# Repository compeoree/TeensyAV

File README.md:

# TeensyAV
A two-layer printed circuit board that breaks out a Teensy 3.5 or 3.6. Its primary goal is to provide a front end for the [Teensy Convolution Sofware Defined Radio](https://github.com/compeoree/Teensy-ConvolutionSDR), but can be used for any audio/video project. 

# UNTESTED!
This is a work in progress and has yet to be fabricated, assembled, or tested.

# Easy Method
* Order PCB through [OSHPark](https://oshpark.com/shared_projects/IBIkLilf)

# DIY Method
* Install KiCad version 5 (http://kicad-pcb.org/download/)
* Copy Library and Modules to KiCad install directory (usually {install_location}/KiCad/share/kicad/)
* Open TeensyAV.pro project file

## BOM (Total price approximately $90)
* PCB ([$18.68](https://oshpark.com/shared_projects/IBIkLilf))
* U1 Teensy 3.6 ([$29.25](https://www.pjrc.com/store/teensy36.html))
* J1 Audio Board ([$14.25](https://www.pjrc.com/store/teensy3_audio.html))
* U2 Touchscreen ([$15.00](https://www.pjrc.com/store/display_ili9341_touch.html))
* Q1 Si2371EDS MOSFET ([$0.49](https://www.mouser.com/ProductDetail/78-SI2371EDS-T1-GE3))
* Q2 BSR802N MOSFET ([$0.46](https://www.mouser.com/ProductDetail/726-BSR802NL6327))
* S1,S2,S3,S4,S5,S7 Switches ([$0.25](https://www.mouser.com/ProductDetail/653-B3F-1000))
* SW1,SW2,SW3 Magnetic Encoder ([$1.14](https://www.mouser.com/ProductDetail/858-EN12-HS22AF20))
* SW4 Optional Optical Encoder ([$28.30](https://www.mouser.com/ProductDetail/652-EM14A0D-B28L064N))
* R1,R2,R3,R4 10K SMD Resistor ([$0.10](https://www.mouser.com/ProductDetail/603-RC0603FR-0710KL))
* CR2032 RTC Battery and Holder ([$0.29](https://www.mouser.com/ProductDetail/712-BAT-HLD-001))
* J1,J2 SMD male headers ([$2.10](https://www.mouser.com/ProductDetail/710-61001418221))
* U1 SMD male headers (left) ([$3.61](https://www.mouser.com/ProductDetail/710-61002418221))

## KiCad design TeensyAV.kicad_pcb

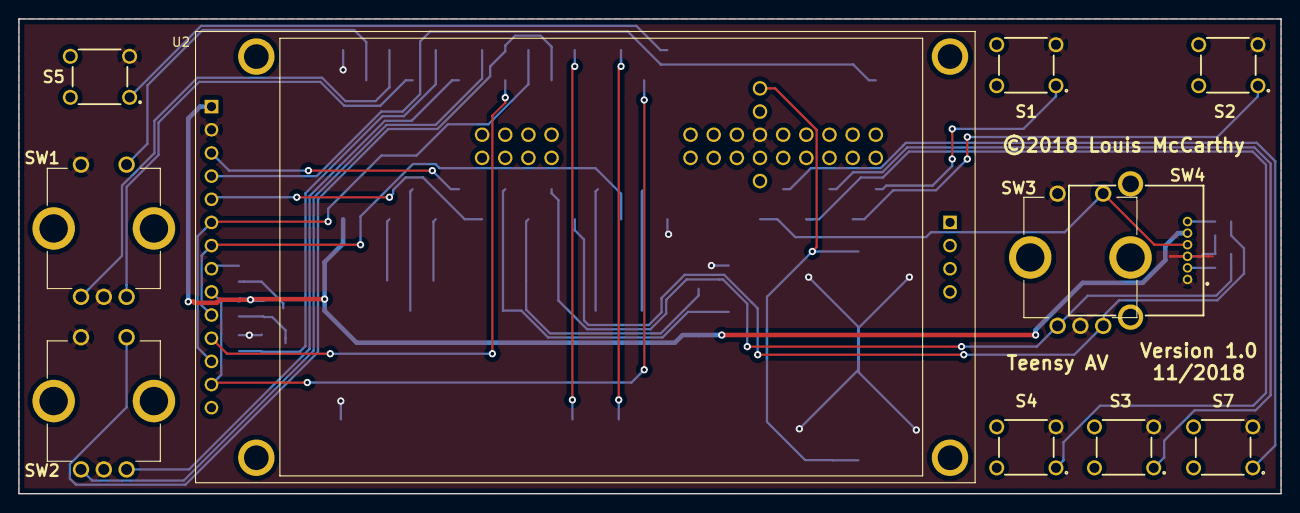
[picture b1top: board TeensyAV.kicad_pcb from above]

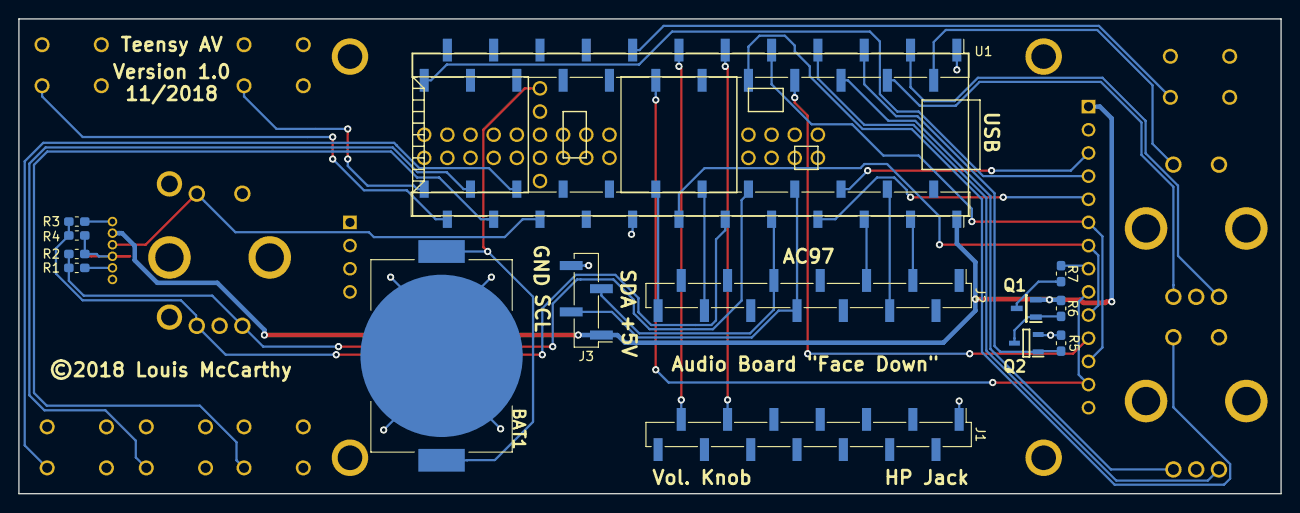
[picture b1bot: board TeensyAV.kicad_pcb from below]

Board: 2 copper layers, 138.4 x 52.1 mm, 25 parts (14 on the bottom side), 40 nets.

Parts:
BAT1: BAT-HLD-001; BATHLD001
J1, J2: Conn_01x14_Male; PinHeader_1x14_P2.54mm_Vertical_SMD_Pin1Left
J3: Conn_01x04_Male; PinHeader_1x04_P2.54mm_Vertical_SMD_Pin1Left
Q1: SI2371EDS-T1-GE3; SOT95P237X112-3N
Q2: BSR802N_L6327; SOT95P285X120-3N
R1, R2, R3, R4, R5, R6: 10K; R_0603_1608Metric_Pad1.05x0.95mm_HandSolder
R7: 100R; R_0603_1608Metric_Pad1.05x0.95mm_HandSolder
S1, S2, S3, S4, S5, S7: B3F-1000; B3F1002
SW1, SW2, SW3: EN12-HS22AF20; EN12HS22AF20
SW4: EM14A0D-C24-L064S; EM14A0D(AXIAL)
U1: Teensy3.6; Teensy35_36_SMD
U2: ILI9341_TOUCH

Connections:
+3V3: J2.3, U1.51
+5V: J3.1, Q1.2, R6.2, SW4.5, U1.53, U2.1
/Backlight: Q2.1, R5.2, U1.5
B1: S1.1, U1.30
B2: S2.1, U1.31
B3: S3.1, U1.32
B4: S4.1, U1.33
B5: SW3.E1, SW4.4, U1.35
B7: S7.1, U1.34
BCLK: J1.11, U1.11
GND: BAT1.3, J1.1, J3.4, Q2.2, R2.2, R4.2, R5.1, S1.3, S2.3, S3.3, S4.3, S5.3, S7.3, SW1.C1, SW1.D1, SW2.C1, SW2.D1, SW3.C1, SW3.D1, SW4.1, SW4.3, U1.1, U1.27, U1.39, U2.2
LRCLK: J2.4, U1.50
MCLK: J1.13, U1.13
MISO: U1.14, U2.9, U2.13
MOSI: U1.9, U2.6, U2.12
unnamed: BAT1.1, BAT1.2, U1.25
unnamed: Q1.1, Q2.3, R6.1
unnamed: Q1.3, R7.1
unnamed: R1.1, SW4.2
unnamed: R1.2, R2.1, SW3.A1, U1.44
unnamed: R3.1, SW4.6
unnamed: R3.2, R4.1, SW3.B1, U1.43
unnamed: R7.2, U2.8
unnamed: SW1.A1, U1.3
unnamed: SW1.B1, U1.4
unnamed: SW1.E1, U1.2
unnamed: SW2.A1, U1.7
unnamed: SW2.B1, U1.6
unnamed: SW2.E1, U1.10
PWR: S5.1, U1.15
RX: J2.14, U1.40
SCL: J2.8, J3.2, U1.46
SCLK: U1.41, U2.7, U2.10
SDA: J2.9, J3.3, U1.45
TFT_CS: U1.48, U2.3
TFT_DC: U1.47, U2.5
TFT_RST: U1.24, U2.4
TX: J2.5, U1.49
T_CS: U1.8, U2.11
VOL: J2.12, U1.42

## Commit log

2018-11-19 Added OSHPark permalink
2018-11-19 Initial files added
2018-11-19 Updated BOM and added images
2018-11-19 Updated BOM

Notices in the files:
TeensyAV.kicad_pcb:
©2018 Louis McCarthy
